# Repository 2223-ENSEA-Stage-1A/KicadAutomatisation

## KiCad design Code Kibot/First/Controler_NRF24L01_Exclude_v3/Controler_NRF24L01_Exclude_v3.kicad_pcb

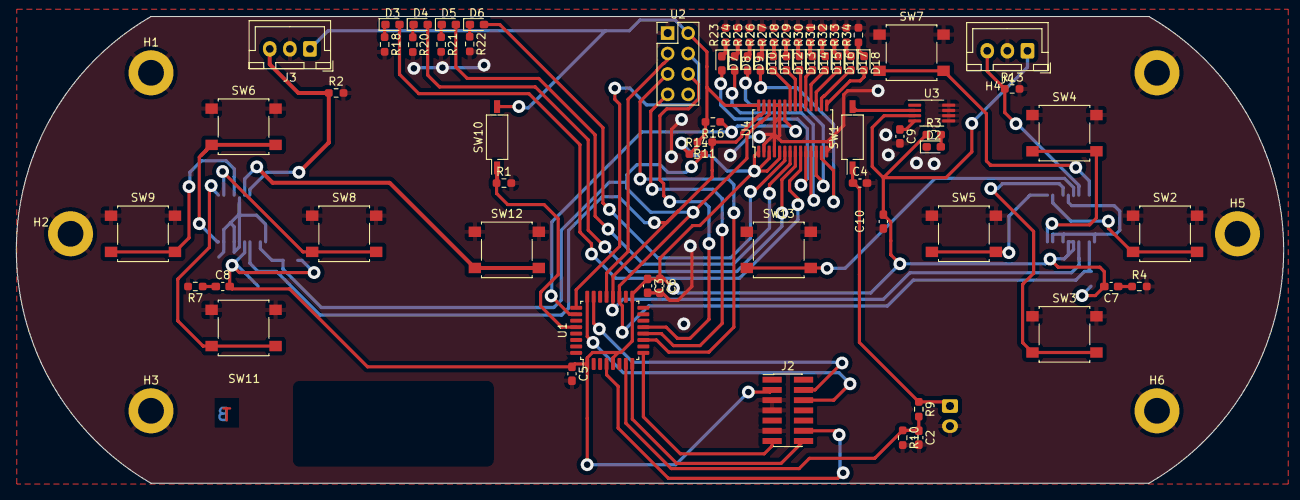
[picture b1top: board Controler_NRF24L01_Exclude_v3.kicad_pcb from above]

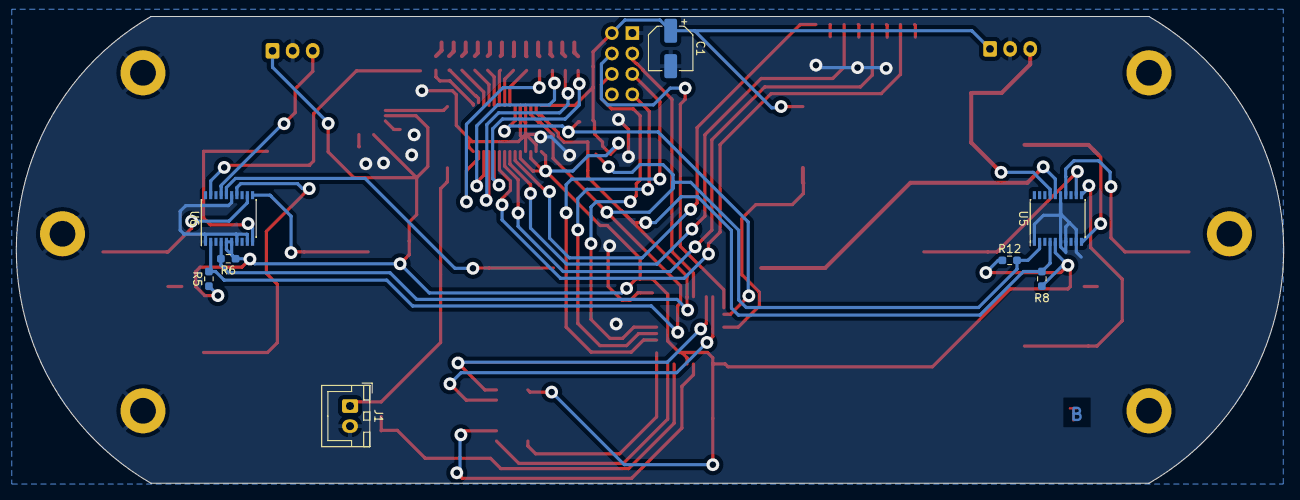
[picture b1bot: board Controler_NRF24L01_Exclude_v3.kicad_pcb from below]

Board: 2 copper layers, 157.5 x 58.0 mm, 87 parts (8 on the bottom side), 68 nets.

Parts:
C1: 22uF; CP_Elec_5x5.4
C2: 1nF; C_0603_1608Metric_Pad1.08x0.95mm_HandSolder
C3, C5: 100n; C_0603_1608Metric_Pad1.08x0.95mm_HandSolder
C4: 1u; C_0603_1608Metric_Pad1.08x0.95mm_HandSolder
C6: 10u; C_0603_1608Metric_Pad1.08x0.95mm_HandSolder
C7, C8, C10: 100nF; C_0603_1608Metric_Pad1.08x0.95mm_HandSolder
C9: 470p; C_0603_1608Metric_Pad1.08x0.95mm_HandSolder
D2: LED_Small; LED_0603_1608Metric_Pad1.05x0.95mm_HandSolder
D3: G1; LED_0603_1608Metric_Pad1.05x0.95mm_HandSolder
D4: G2; LED_0603_1608Metric_Pad1.05x0.95mm_HandSolder
D5: G3; LED_0603_1608Metric_Pad1.05x0.95mm_HandSolder
D6: G4; LED_0603_1608Metric_Pad1.05x0.95mm_HandSolder
D7: G5; LED_0603_1608Metric_Pad1.05x0.95mm_HandSolder
D8: G6; LED_0603_1608Metric_Pad1.05x0.95mm_HandSolder
D9: G7; LED_0603_1608Metric_Pad1.05x0.95mm_HandSolder
D10: G8; LED_0603_1608Metric_Pad1.05x0.95mm_HandSolder
D11: O1; LED_0603_1608Metric_Pad1.05x0.95mm_HandSolder
D12: O2; LED_0603_1608Metric_Pad1.05x0.95mm_HandSolder
D13: O3; LED_0603_1608Metric_Pad1.05x0.95mm_HandSolder
D14: O4; LED_0603_1608Metric_Pad1.05x0.95mm_HandSolder
D15: R1; LED_0603_1608Metric_Pad1.05x0.95mm_HandSolder
D16: R2; LED_0603_1608Metric_Pad1.05x0.95mm_HandSolder
D17: R3; LED_0603_1608Metric_Pad1.05x0.95mm_HandSolder
D18: R4; LED_0603_1608Metric_Pad1.05x0.95mm_HandSolder
H1, H2, H3, H4, H5, H6: MountingHole_Pad; MountingHole_3.2mm_M3_DIN965_Pad
J1: Conn_01x02; JST_XH_B2B-XH-A_1x02_P2.50mm_Vertical
J2: Conn_02x07_Odd_Even; PinHeader_2x07_P1.27mm_Vertical_SMD
J3, J4: Conn_01x03; JST_XH_B3B-XH-A_1x03_P2.50mm_Vertical
R1, R2, R3, R13, R18, R20, R21, R22, R23, R24, R25, R26, R27, R28, R29, R30, R31, R32, R33, R34: 1K; R_0603_1608Metric_Pad0.98x0.95mm_HandSolder
R4, R7: 1k; R_0603_1608Metric_Pad0.98x0.95mm_HandSolder
R5, R6, R8, R11, R12, R14, R16: 10K; R_0603_1608Metric_Pad0.98x0.95mm_HandSolder
R9, R10: 1M; R_0603_1608Metric_Pad0.98x0.95mm_HandSolder
SW1, SW10: SW_DIP_x01; SW_DIP_SPSTx01_Slide_Copal_CHS-01B_W7.62mm_P1.27mm
SW2, SW3, SW4, SW5, SW6, SW8, SW9, SW11, SW12, SW13: SW_Push; SW_SPST_B3S-1000
SW7: SW_SPST; SW_SPST_B3S-1000
U1: STM32L412KBTx; LQFP-32_7x7mm_P0.8mm
U2: nRF24_Full; PinHeader_2x04_P2.54mm_Vertical
U3: MIC5219-3.3YMM; MSOP-8_3x3mm_P0.65mm
U4: PCA9685PW; TSSOP-28_4.4x9.7mm_P0.65mm
U5, U6: PCF8574TS; SSOP-20_4.4x6.5mm_P0.65mm

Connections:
A_Button: SW2.2, U6.12 (P2)
B_Button: SW3.2, U6.14 (P3)
CSN_nRF24: U1.25 (PA15), U2.4 (CSN)
DC_Button: SW11.2, U5.11 (P1)
DIODE_OE: R16.1, U1.26 (PB3), U4.23 (~OE)
DIO/EX_CLK: R5.2, R12.2, R14.2, U1.19 (PA9), U4.26 (SCL), U5.2 (SCL), U6.2 (SCL)
DIO/EX_SDA: R6.2, R8.2, R11.1, U1.20 (PA10), U4.27 (SDA), U5.4 (SDA), U6.4 (SDA)
Digital_Out_Put: U1.12 (PA6), U2.7 (MISO)
GND: C1.2, C2.2, C3.2, C4.2, C5.2, C6.2, C9.2, C10.2, D2.1 (K), H1.1, H2.1, H3.1, H4.1, H5.1, H6.1, J1.2, J2.5, J2.7, J2.11, J3.2, J4.2, R1.2, R2.2, R4.2, R7.2, R10.2, R13.2, R18.2, R20.2, R21.2, R22.2, R23.2, R24.2, R25.2, R26.2, R27.2, R28.2, R29.2, R30.2, R31.2, R32.2, R33.2, R34.2, SW2.1, SW3.1, SW4.1, SW5.1, SW6.1, SW7.1 (A), SW8.1, SW9.1, SW11.1, SW12.1, SW13.1, U1.16 (VSS), U1.32 (VSS), U2.1 (GND), U3.5 (GND), U3.6 (GND), U3.7 (GND), U3.8 (GND), U4.2 (A1), U4.4 (A3), U4.14 (VSS), U4.24 (A5), U4.25 (EXTCLK), U5.1 (~INT), U5.6 (A0), U5.7 (A1), U5.9 (A2), U5.15 (VSS), U6.1 (~INT), U6.7 (A1), U6.9 (A2), U6.15 (VSS)
Glob_Alim: C1.1, C3.1, C5.1, C6.1, C7.2, C8.2, C10.1, J2.3, J3.1, J4.1, R3.1, R5.1, R6.1, R8.1, R11.2, R12.1, R14.1, R16.2, SW10.2, U1.1 (VDD), U1.5 (VDDA), U1.17 (VDD), U2.2 (VCC), U3.3 (OUT), U4.1 (A0), U4.3 (A2), U4.5 (A4), U4.28 (VDD), U5.5 (VDD), U6.5 (VDD), U6.6 (A0)
L: J4.3, R13.1, U6.17 (P5)
LC_Button: SW8.2, U5.12 (P2)
Li-ion: C4.1, J1.1, R9.1, SW1.1
MOSI: U1.13 (PA7), U2.6 (MOSI)
NES/SNES_switcher: R1.1, SW10.1, U1.28 (PB5)
unnamed: SW1.2, U3.2 (IN)
unnamed: C7.1, R4.1
unnamed: C8.1, R7.1
unnamed: D2.2 (A), R3.2
unnamed: D3.2 (A), U4.9 (LED3)
unnamed: D3.1 (K), R18.1
unnamed: D4.2 (A), U4.8 (LED2)
unnamed: D4.1 (K), R20.1
unnamed: D5.2 (A), U4.7 (LED1)
unnamed: D5.1 (K), R21.1
unnamed: D6.2 (A), U4.6 (LED0)
unnamed: D6.1 (K), R22.1
unnamed: D7.2 (A), U4.10 (LED4)
unnamed: D7.1 (K), R23.1
unnamed: D8.2 (A), U4.11 (LED5)
unnamed: D8.1 (K), R24.1
unnamed: D9.2 (A), U4.12 (LED6)
unnamed: D9.1 (K), R25.1
unnamed: D10.2 (A), U4.13 (LED7)
unnamed: D10.1 (K), R26.1
unnamed: D11.2 (A), U4.22 (LED15)
unnamed: D11.1 (K), R27.1
unnamed: D12.2 (A), U4.21 (LED14)
unnamed: D12.1 (K), R28.1
unnamed: D13.2 (A), U4.20 (LED13)
unnamed: D13.1 (K), R29.1
unnamed: D14.2 (A), U4.19 (LED12)
unnamed: D14.1 (K), R30.1
unnamed: D15.2 (A), U4.18 (LED11)
unnamed: D15.1 (K), R31.1
unnamed: D16.2 (A), U4.17 (LED10)
unnamed: D16.1 (K), R32.1
unnamed: D17.2 (A), U4.16 (LED9)
unnamed: D17.1 (K), R33.1
unnamed: D18.2 (A), U4.15 (LED8)
unnamed: D18.1 (K), R34.1
unnamed: C9.1, U3.4 (BP)
Order_Search: SW7.2 (B), U6.19 (P6)
POWER_CHECK: C2.1, R9.2, R10.1, U1.7 (PA1)
Pin_Clock: U1.11 (PA5), U2.5 (SCK)
R: J3.3, R2.1, U5.17 (P5)
RC_Button: SW9.2, U5.14 (P3)
RX/TX: U1.21 (PA11), U2.3 (CE)
Reset_Buton: J2.12, U1.4 (NRST)
SE_Button: SW13.2, U6.16 (P4)
ST_Button: SW12.2, U5.16 (P4)
SWDCK: J2.6, U1.24 (PA14)
SWDIO: J2.4, U1.23 (PA13)
UC_Button: SW6.2, U5.10 (P0)
USART2_RX: J2.13, U1.9 (PA3)
USART2_TX: J2.14, U1.8 (PA2)
X_Button: SW4.2, U6.10 (P0)
Y_Button: SW5.2, U6.11 (P1)

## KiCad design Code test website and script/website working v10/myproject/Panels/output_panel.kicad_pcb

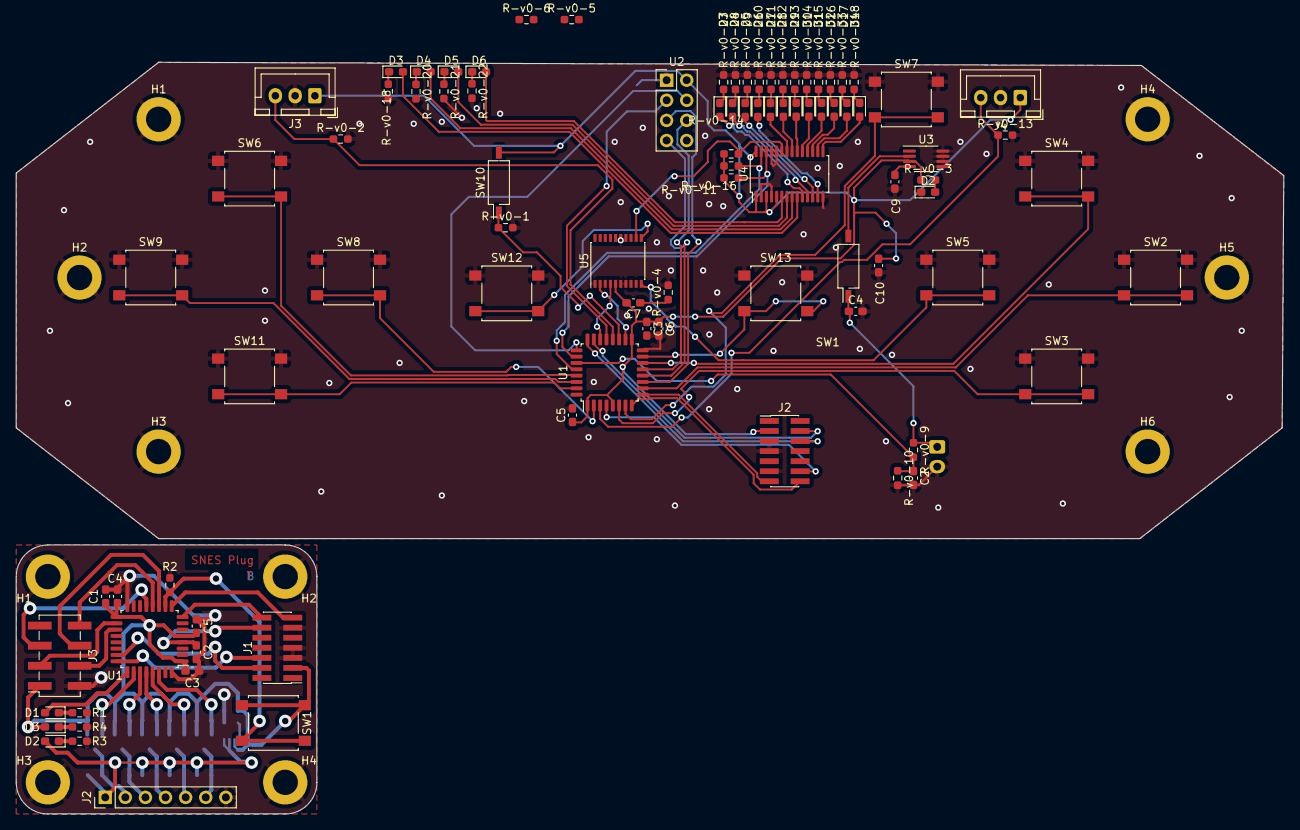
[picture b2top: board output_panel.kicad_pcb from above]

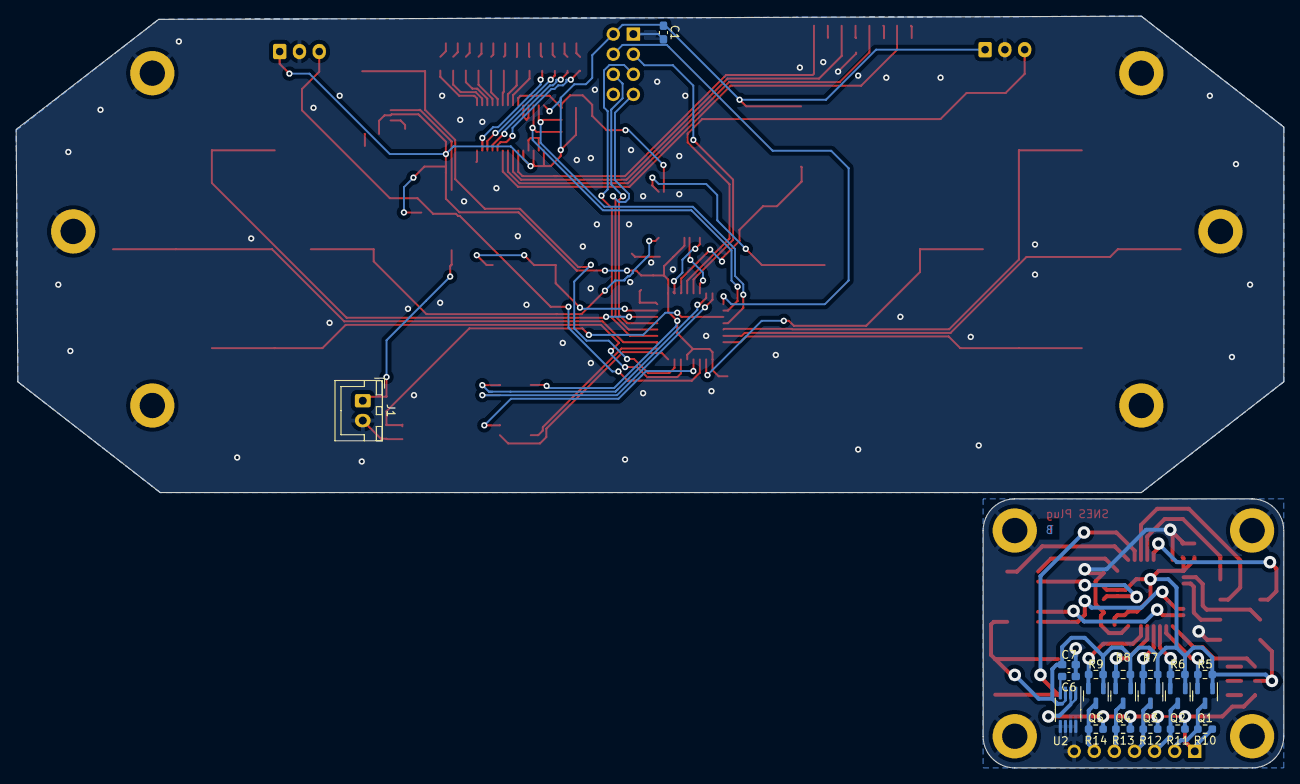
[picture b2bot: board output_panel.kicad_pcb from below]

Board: 2 copper layers, 160.2 x 95.0 mm, 121 parts (20 on the bottom side), 98 nets.

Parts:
C1, C6: 10u; C_0603_1608Metric_Pad1.08x0.95mm_HandSolder
C1#2: 100uF; C_0603_1608Metric_Pad1.08x0.95mm_HandSolder
C2, C3, C3#2, C4, C5, C5#2: 100n; C_0603_1608Metric_Pad1.08x0.95mm_HandSolder
C2#2: 1nF; C_0603_1608Metric_Pad1.08x0.95mm_HandSolder
C4#2: 1u; C_0603_1608Metric_Pad1.08x0.95mm_HandSolder
C6#2, C9: 470p; C_0603_1608Metric_Pad1.08x0.95mm_HandSolder
C7: 100µF; C_0603_1608Metric_Pad1.08x0.95mm_HandSolder
C7#2: 2.2u; C_0603_1608Metric_Pad1.08x0.95mm_HandSolder
C10: 100nF; C_0603_1608Metric_Pad1.08x0.95mm_HandSolder
D1, D2#2: LED_Small; D_0603_1608Metric_Pad1.05x0.95mm_HandSolder
D2: L-v0-ED_Small; L-v0-ED_0603_1608Metric_Pad1.05x0.95mm_HandSolder
D3: LED; D_0603_1608Metric_Pad1.05x0.95mm_HandSolder
D3#2: G1; L-v0-ED_0603_1608Metric_Pad1.05x0.95mm_HandSolder
D4: G2; L-v0-ED_0603_1608Metric_Pad1.05x0.95mm_HandSolder
D5: G3; L-v0-ED_0603_1608Metric_Pad1.05x0.95mm_HandSolder
D6: G4; L-v0-ED_0603_1608Metric_Pad1.05x0.95mm_HandSolder
D7: G5; L-v0-ED_0603_1608Metric_Pad1.05x0.95mm_HandSolder
D8: G6; L-v0-ED_0603_1608Metric_Pad1.05x0.95mm_HandSolder
D9: G7; L-v0-ED_0603_1608Metric_Pad1.05x0.95mm_HandSolder
D10: G8; L-v0-ED_0603_1608Metric_Pad1.05x0.95mm_HandSolder
D11: O1; L-v0-ED_0603_1608Metric_Pad1.05x0.95mm_HandSolder
D12: O2; L-v0-ED_0603_1608Metric_Pad1.05x0.95mm_HandSolder
D13: O3; L-v0-ED_0603_1608Metric_Pad1.05x0.95mm_HandSolder
D14: O4; L-v0-ED_0603_1608Metric_Pad1.05x0.95mm_HandSolder
D15: R-v0-1; L-v0-ED_0603_1608Metric_Pad1.05x0.95mm_HandSolder
D16: R-v0-2; L-v0-ED_0603_1608Metric_Pad1.05x0.95mm_HandSolder
D17: R-v0-3; L-v0-ED_0603_1608Metric_Pad1.05x0.95mm_HandSolder
D18: R-v0-4; L-v0-ED_0603_1608Metric_Pad1.05x0.95mm_HandSolder
H1, H1#2, H2, H2#2, H3, H3#2, H4, H4#2, H5, H6: MountingHole_Pad; MountingHole_3.2mm_M3_DIN965_Pad
J1, J2#2: Conn_02x07_Odd_Even; PinHeader_2x07_P1.27mm_Vertical_SMD
J1#2: Conn_01x02; JST_XH_B2B-XH-A_1x02_P2.50mm_Vertical
J2: Conn_01x07_Socket; PinHeader_1x07_P2.54mm_Vertical
J3, J4: Conn_01x03; JST_XH_B3B-XH-A_1x03_P2.50mm_Vertical
J3#2: Conn_01x08_Socket; PinSocket_2x04_P2.54mm_Vertical_SMD
Q1, Q2, Q3, Q4, Q5: 2N7002; SOT-23
R1, R3, R4: 1k; R_0603_1608Metric_Pad0.98x0.95mm_HandSolder
R2, R5, R6, R7, R8, R9, R10, R11, R12, R13, R14: 10k; R_0603_1608Metric_Pad0.98x0.95mm_HandSolder
R-v0-1, R-v0-2, R-v0-3, R-v0-5, R-v0-6, R-v0-13, R-v0-18, R-v0-20, R-v0-21, R-v0-22, R-v0-23, R-v0-24, R-v0-25, R-v0-26, R-v0-27, R-v0-28, R-v0-29, R-v0-30, R-v0-31, R-v0-32, R-v0-33, R-v0-34: 1K; R-v0-_0603_1608Metric_Pad0.98x0.95mm_HandSolder
R-v0-4: 10k; R-v0-_0603_1608Metric_Pad0.98x0.95mm_HandSolder
R-v0-9, R-v0-10: 1M; R-v0-_0603_1608Metric_Pad0.98x0.95mm_HandSolder
R-v0-11, R-v0-14, R-v0-16: 10K; R-v0-_0603_1608Metric_Pad0.98x0.95mm_HandSolder
SW1, SW10: SW_DIP_x01; SW_DIP_SPSTx01_Slide_Copal_CHS-01B_W7.62mm_P1.27mm
SW1#2, SW7: SW_SPST; SW_SPST_B3S-1000
SW2, SW3, SW4, SW5, SW6, SW8, SW9, SW11, SW12, SW13: SW_Push; SW_SPST_B3S-1000
U1: STM32L-v0-412KBTx; L-v0-QFP-32_7x7mm_P0.8mm
U1#2: STM32L412KBTx; LQFP-32_7x7mm_P0.8mm
U2: nR-v0-F24_Full; PinHeader_2x04_P2.54mm_Vertical
U2#2, U3: MIC5219-3.3YMM; MSOP-8_3x3mm_P0.65mm
U4: PCA9685PW; TSSOP-28_4.4x9.7mm_P0.65mm
U5: PCF8574TS; SSOP-20_4.4x6.5mm_P0.65mm

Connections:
+3.3V-v1-: C1.1, C3#2.1, C4.1, C5#2.1, C7#2.1, D3.2 (A), J1.3, J3#2.1, Q1.1 (G), Q2.1 (G), Q3.1 (G), Q4.1 (G), Q5.1 (G), R5.1, R6.1, R7.1, R8.1, R9.1, SW1#2.2 (B), U1#2.1 (VDD), U1#2.5 (VDDA), U1#2.17 (VDD), U2#2.3 (OUT)
+5V-v1-: D2#2.2 (A), J2.1, R10.1, R11.1, R12.1, R13.1, R14.1, U2#2.1 (EN), U2#2.2 (IN)
A_Button-v0-: SW2.2, U1.10 (PA4)
Appairing_Btn-v1-: R2.1, SW1#2.1 (A), U1#2.10 (PA4)
B_Button-v0-: SW3.2, U1.6 (PA0)
CSN_nR-v0-F24: U1.25 (PA15), U2.4 (CSN)
Chip_Enable-v1-: J3#2.4, U1#2.19 (PA9)
DC_Button-v0-: SW11.2, U1.31 (PH3)
DIODE_CL-v0-K: R-v0-14.2, U1.26 (PB3), U4.26 (SCL-v0-)
DIODE_OE-v0-: R-v0-16.1, U4.23 (~OE), U5.12 (P2)
DIODE_SDA-v0-: R-v0-11.1, U1.28 (PB5), U4.27 (SDA)
Data_Clock_SNES-v1-: J2.2, Q1.3 (D), R10.2
Data_Clock_STM32-v1-: Q1.2 (S), R5.2, U1#2.26 (PB3)
Data_Latch_SNES-v1-: J2.3, Q2.3 (D), R11.2
Data_Latch_STM32-v1-: Q2.2 (S), R6.2, U1#2.27 (PB4)
Digital_Out_Put-v0-: U1.12 (PA6), U2.7 (MISO)
GND-v0-: C1#2.2, C2#2.2, C3.2, C4#2.2, C5.2, C6.2, C9.2, C10.2, D2.1 (K), H1.1, H2.1, H3.1, H4#2.1, H5.1, H6.1, J1#2.2, J2#2.5, J2#2.7, J2#2.11, J3.2, J4.2, R-v0-1.2, R-v0-2.2, R-v0-4.2, R-v0-10.2, R-v0-13.2, R-v0-18.2, R-v0-20.2, R-v0-21.2, R-v0-22.2, R-v0-23.2, R-v0-24.2, R-v0-25.2, R-v0-26.2, R-v0-27.2, R-v0-28.2, R-v0-29.2, R-v0-30.2, R-v0-31.2, R-v0-32.2, R-v0-33.2, R-v0-34.2, SW2.1, SW3.1, SW4.1, SW5.1, SW6.1, SW7.1 (A), SW8.1, SW9.1, SW11.1, SW12.1, SW13.1, U1.16 (VSS), U1.32 (VSS), U2.1 (GND-v0-), U3.5 (GND-v0-), U3.6 (GND-v0-), U3.7 (GND-v0-), U3.8 (GND-v0-), U4.2 (A1), U4.4 (A3), U4.14 (VSS), U4.24 (A5), U4.25 (EXTCL-v0-K), U5.1 (~INT), U5.6 (A0), U5.7 (A1), U5.9 (A2), U5.15 (VSS)
GND-v1-: C1.2, C2.1, C3#2.2, C4.2, C5#2.2, C6#2.2, C7#2.2, H1#2.1, H2#2.1, H3#2.1, H4.1, J1.5, J1.7, J1.11, J2.7, J3#2.2, R1.2, R2.2, R3.2, R4.2, U1#2.16 (VSS), U1#2.32 (VSS), U2#2.5 (GND-v1-), U2#2.6 (GND-v1-), U2#2.7 (GND-v1-), U2#2.8 (GND-v1-)
GPIO_EX_CL-v0-K: R-v0-5.2, U1.18 (PA8), U5.2 (SCL-v0-)
GPIO_EX_SER-v0-IAL-v0-_DATA: R-v0-6.2, U1.22 (PA12), U5.4 (SDA)
Glob_Alim-v0-: C1#2.1, C3.1, C5.1, C6.1, C7.2, C10.1, J2#2.3, J3.1, J4.1, R-v0-3.1, R-v0-5.1, R-v0-6.1, R-v0-11.2, R-v0-14.1, R-v0-16.2, SW10.2, U1.1 (VDD), U1.5 (VDDA), U1.17 (VDD), U2.2 (VCC), U3.3 (OUT), U4.1 (A0), U4.3 (A2), U4.5 (A4), U4.28 (VDD), U5.5 (VDD)
IOBit_SNES-v1-: J2.6, Q5.3 (D), R14.2
IOBit_STM32-v1-: Q5.2 (S), R9.2, U1#2.30 (PB7)
L-v0-: J4.3, R-v0-13.1, U1.3 (PC15)
L-v0-C_Button-v0-: SW8.2, U1.2 (PC14)
L-v0-i-ion-v0-: C4#2.1, J1#2.1, R-v0-9.1, SW1.1
MOSI-v0-: U1.13 (PA7), U2.6 (MOSI-v0-)
NES/SNES_switcher-v0-: R-v0-1.1, SW10.1, U1.19 (PA9)
NRST-v1-: C2.2, J1.12, U1#2.4 (NRST-v1-)
unnamed: C7.1, R-v0-4.1
unnamed: D1.1 (K), R1.1
unnamed: D2.2 (A), R-v0-3.2
unnamed: D2#2.1 (K), R3.1
unnamed: D3#2.2 (A), U4.9 (L-v0-ED3)
unnamed: D3#2.1 (K), R-v0-18.1
unnamed: D3.1 (K), R4.1
unnamed: D4.2 (A), U4.8 (L-v0-ED2)
unnamed: D4.1 (K), R-v0-20.1
unnamed: D5.2 (A), U4.7 (L-v0-ED1)
unnamed: D5.1 (K), R-v0-21.1
unnamed: D6.2 (A), U4.6 (L-v0-ED0)
unnamed: D6.1 (K), R-v0-22.1
unnamed: D7.2 (A), U4.10 (L-v0-ED4)
unnamed: D7.1 (K), R-v0-23.1
unnamed: D8.2 (A), U4.11 (L-v0-ED5)
unnamed: D8.1 (K), R-v0-24.1
unnamed: D9.2 (A), U4.12 (L-v0-ED6)
unnamed: D9.1 (K), R-v0-25.1
unnamed: D10.2 (A), U4.13 (L-v0-ED7)
unnamed: D10.1 (K), R-v0-26.1
unnamed: D11.2 (A), U4.22 (L-v0-ED15)
unnamed: D11.1 (K), R-v0-27.1
unnamed: D12.2 (A), U4.21 (L-v0-ED14)
unnamed: D12.1 (K), R-v0-28.1
unnamed: D13.2 (A), U4.20 (L-v0-ED13)
unnamed: D13.1 (K), R-v0-29.1
unnamed: D14.2 (A), U4.19 (L-v0-ED12)
unnamed: D14.1 (K), R-v0-30.1
unnamed: D15.2 (A), U4.18 (L-v0-ED11)
unnamed: D15.1 (K), R-v0-31.1
unnamed: D16.2 (A), U4.17 (L-v0-ED10)
unnamed: D16.1 (K), R-v0-32.1
unnamed: D17.2 (A), U4.16 (L-v0-ED9)
unnamed: D17.1 (K), R-v0-33.1
unnamed: D18.2 (A), U4.15 (L-v0-ED8)
unnamed: D18.1 (K), R-v0-34.1
unnamed: C6#2.1, U2#2.4 (BP)
unnamed: C9.1, U3.4 (BP)
unnamed: SW1.2, U3.2 (IN)
Order_Search-v0-: SW7.2 (B), U1.7 (PA1)
POWER-v0-_CHECK-v0-: C2#2.1, R-v0-9.2, R-v0-10.1, U1.27 (PB4)
Pin_Clock-v0-: U1.11 (PA5), U2.5 (SCK)
R-v0-: J3.3, R-v0-2.1, U1.20 (PA10)
R-v0-C_Button: SW9.2, U1.30 (PB7)
R-v0-X/TX: U1.21 (PA11), U2.3 (CE)
R-v0-eset_Buton -v0-: J2#2.12, U1.4 (NR-v0-ST)
SE_Button-v0-: SW13.2, U1.15 (PB1)
SPI_Chip_Select-v1-: J3#2.3, U1#2.18 (PA8)
SPI_Clock-v1-: J3#2.6, U1#2.11 (PA5)
SPI_Digital_Input-v1-: J3#2.8, U1#2.12 (PA6)
SPI_Digital_Output-v1-: J3#2.5, U1#2.13 (PA7)
ST_Button-v0-: SW12.2, U5.11 (P1)
SWDCK-v0-: J2#2.6, U1.24 (PA14)
SWDCK-v1-: J1.6, U1#2.24 (PA14)
SWDIO-v0-: J2#2.4, U1.23 (PA13)
SWDIO-v1-: J1.4, U1#2.23 (PA13)
Serial_Data1_SNES-v1-: J2.4, Q3.3 (D), R12.2
Serial_Data1_STM32-v1-: Q3.2 (S), R7.2, U1#2.28 (PB5)
Serial_Data2_SNES-v1-: J2.5, Q4.3 (D), R13.2
Serial_Data2_STM32-v1-: Q4.2 (S), R8.2, U1#2.29 (PB6)
Status_LED-v1-: D1.2 (A), U1#2.25 (PA15)
UC_Button-v0-: SW6.2, U1.29 (PB6)
USAR-v0-T2_R-v0-X-v0-: J2#2.13, U1.9 (PA3)
USAR-v0-T2_TX-v0-: J2#2.14, U1.8 (PA2)
USART2_RX-v1-: J1.13, U1#2.9 (PA3)
USART2_TX-v1-: J1.14, U1#2.8 (PA2)
X_Button-v0-: SW4.2, U1.14 (PB0)
Y_Button-v0-: SW5.2, U5.10 (P0)
